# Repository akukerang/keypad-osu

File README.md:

# keypad-osu
 2 key keypad for osu. For PCB design practice, not 100% sure if works if it was to be produced.
## Resources used:
- Tokaku keyboard pcb: https://www.youtube.com/watch?v=Ov2vdJQmaAw
- Ai03 PCB Guide: https://wiki.ai03.com/books/pcb-design/page/pcb-guide-part-1---preparations
- Ebastler Marbastlib: https://github.com/ebastler/marbastlib
- Ai03 random-keyboard-parts.pretty: https://github.com/ai03-2725/random-keyboard-parts.pretty
## To do
- Add LED
- Add extra buttons (not switches) for extra functionality
- A case

## Pictures
### PCB

### Top

### Bottom

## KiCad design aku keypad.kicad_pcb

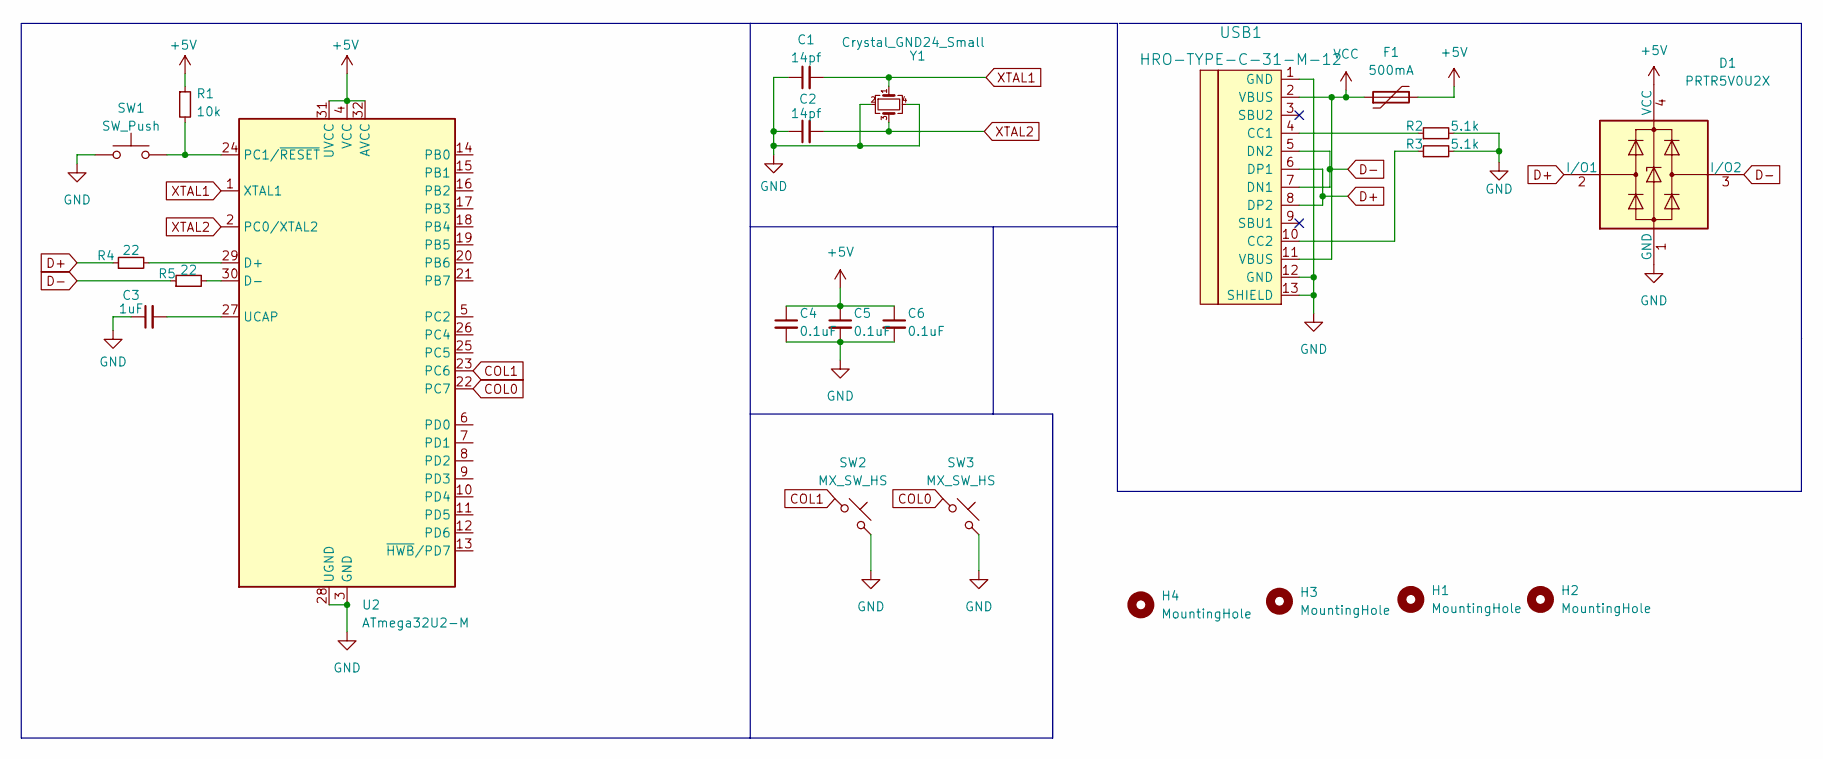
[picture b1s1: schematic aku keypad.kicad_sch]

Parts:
C1, C2: 14pf; C_0402_1005Metric_Pad0.74x0.62mm_HandSolder
C3: 1uF; C_0402_1005Metric_Pad0.74x0.62mm_HandSolder
C4, C5, C6: 0.1uF; C_0402_1005Metric_Pad0.74x0.62mm_HandSolder
D1: PRTR5V0U2X; SOT-143
F1: 500mA; Fuse_0402_1005Metric
H1, H2, H3, H4: MountingHole; Generic-Mounthole
R1: 10k; R_0402_1005Metric_Pad0.72x0.64mm_HandSolder
R2, R3: 5.1k; R_0402_1005Metric_Pad0.72x0.64mm_HandSolder
R4, R5: 22; R_0402_1005Metric_Pad0.72x0.64mm_HandSolder
SW1: SW_Push; SW_SPST_SKQG_WithStem
SW2, SW3: MX_SW_HS; SW_MX_HS_1u
U2: ATmega32U2-M; QFN-32-1EP_5x5mm_P0.5mm_EP3.1x3.1mm
USB1: HRO-TYPE-C-31-M-12; HRO-TYPE-C-31-M-12-HandSoldering
Y1: Crystal_GND24_Small; Crystal_SMD_3225-4Pin_3.2x2.5mm_HandSoldering

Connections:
+5V: C4.1, C5.1, C6.1, D1.4 (VCC), F1.2, R1.1, U2.4 (VCC), U2.31 (UVCC), U2.32 (AVCC)
COL0: SW3.1, U2.22 (PC7)
COL1: SW2.1, U2.23 (PC6)
D+: D1.2 (I/O1), R4.1, USB1.6 (DP1), USB1.8 (DP2)
D-: D1.3 (I/O2), R5.1, USB1.5 (DN2), USB1.7 (DN1)
GND: C1.1, C2.1, C3.1, C4.2, C5.2, C6.2, D1.1 (GND), R2.2, R3.2, SW1.1, SW2.2, SW3.2, U2.3 (GND), U2.28 (UGND), U2.33 (GND), USB1.1 (GND), USB1.12 (GND), USB1.13 (SHIELD), Y1.2, Y1.4
unnamed: C3.2, U2.27 (UCAP)
unnamed: R1.2, SW1.2, U2.24 (PC1/~RESET)
unnamed: R2.1, USB1.4 (CC1)
unnamed: R3.1, USB1.10 (CC2)
unnamed: R4.2, U2.29 (D+)
unnamed: R5.2, U2.30 (D-)
VCC: F1.1, USB1.2 (VBUS), USB1.11 (VBUS)
XTAL1: C1.2, U2.1 (XTAL1), Y1.1
XTAL2: C2.2, U2.2 (PC0/XTAL2), Y1.3

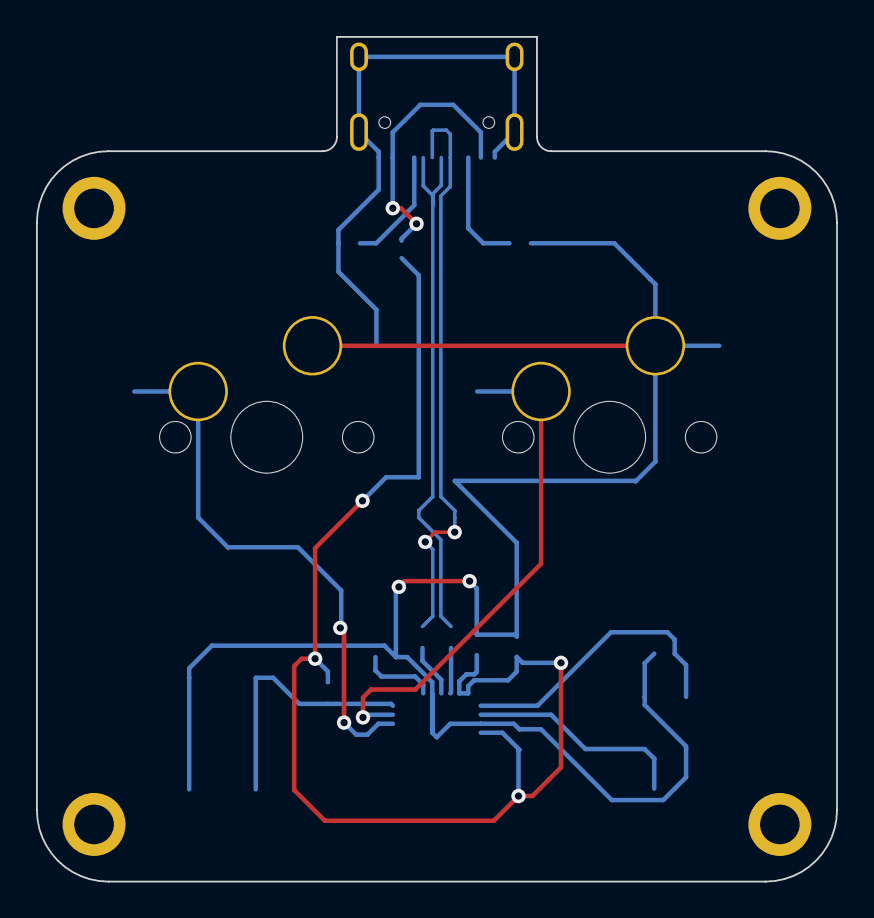
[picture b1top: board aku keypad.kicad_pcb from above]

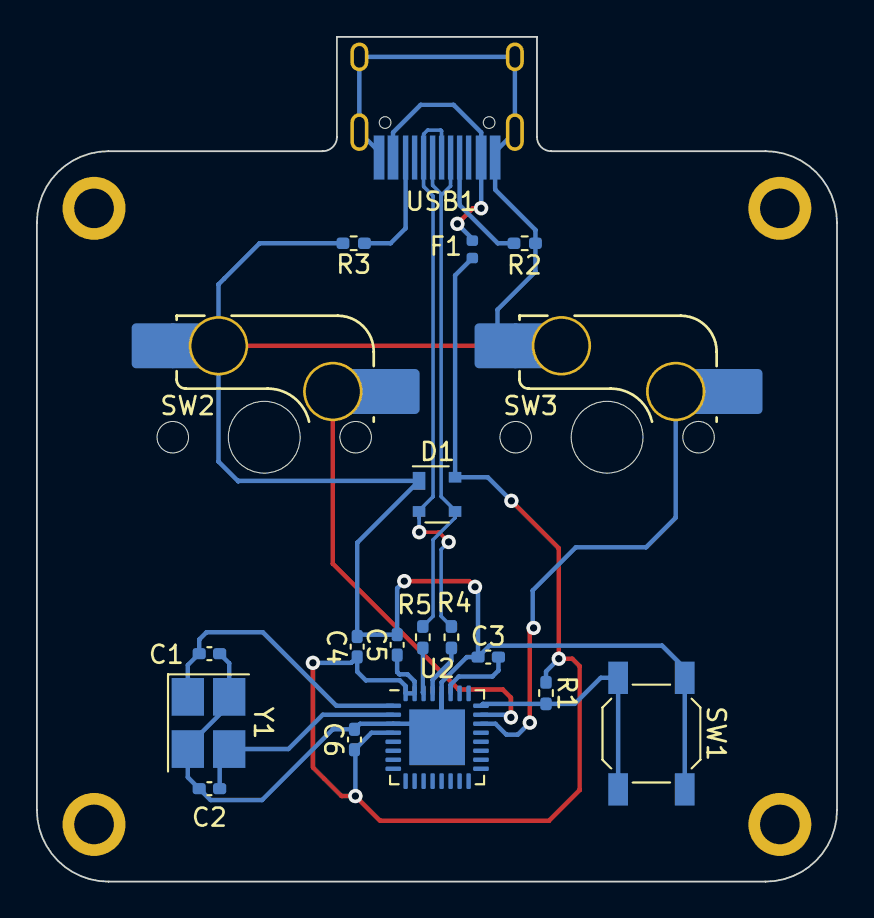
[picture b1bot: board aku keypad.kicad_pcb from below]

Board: 2 copper layers, 44.5 x 46.9 mm, 23 parts (19 on the bottom side), 15 nets.

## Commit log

2022-07-03 init commit
2022-07-03 Update README.md
    added more info
2022-07-03 added pictures
2022-07-03 Added front ground fill
2022-07-03 updated pictures
    front ground fill update
2022-07-03 removed folder to add submodules
2022-07-03 Added random keyboard part submodule
    Also removed marbastlib to make submodule too
2022-07-03 Added marbaslib submodule
2022-08-15 redid routing on pcb
    added type-c submodule, redid routing, changed usb components
2022-08-16 Added mounting holes
2022-08-17 more rerouting, added edge cuts around usb
2022-11-01 removed local files from repo
    added cache and other things to gitignore
2022-11-01 ignore cache
